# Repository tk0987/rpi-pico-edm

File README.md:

# rpi-pico-edm
jusst kicad - for a while

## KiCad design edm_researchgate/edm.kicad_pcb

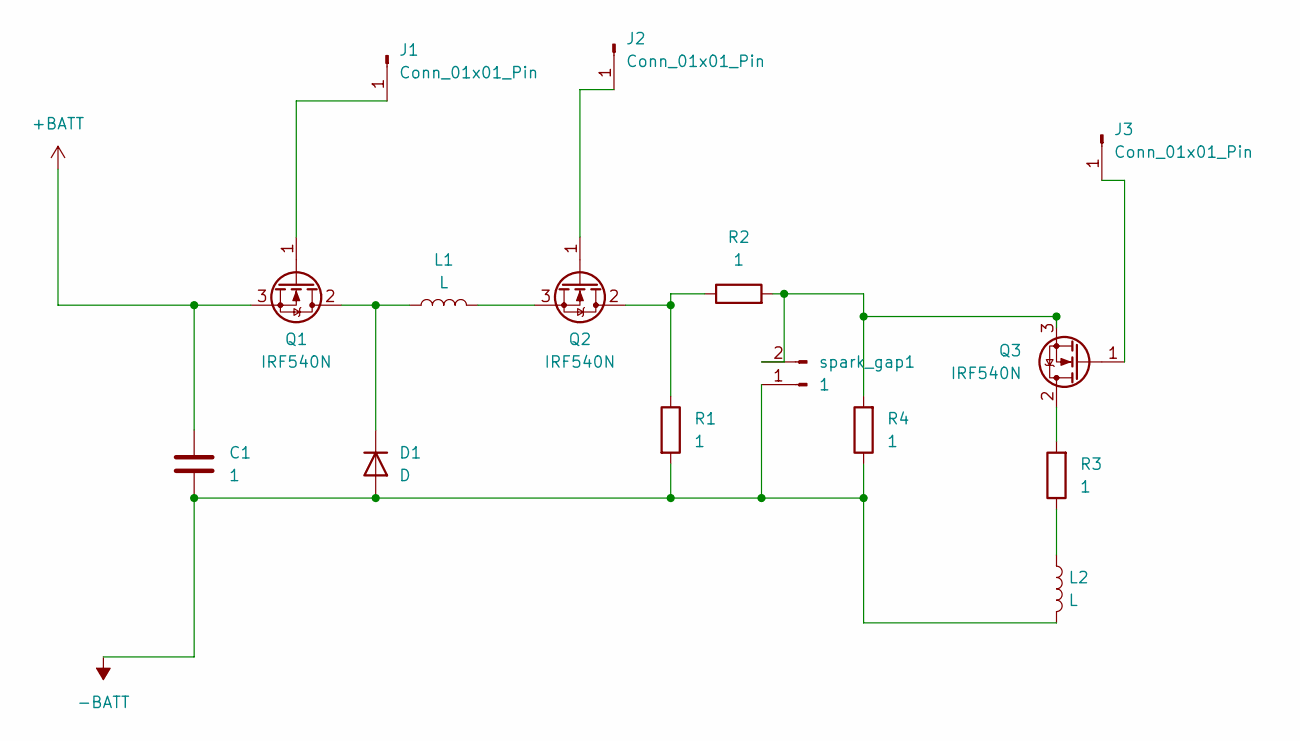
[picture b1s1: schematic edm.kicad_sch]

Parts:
C1: 1; CP_Axial_L37.0mm_D20.0mm_P43.00mm_Horizontal
D1: D; D_5KP_P10.16mm_Horizontal
J1, J2, J3: Conn_01x01_Pin; Pin_D0.7mm_L6.5mm_W1.8mm_FlatFork
L1, L2: L; D_5KP_P10.16mm_Horizontal
Q1, Q2, Q3: IRF540N; TO-220-3_Vertical
R1: 1; R_Axial_DIN0918_L18.0mm_D9.0mm_P25.40mm_Horizontal
R2, R3, R4: 1; R_Axial_DIN0414_L11.9mm_D4.5mm_P20.32mm_Horizontal
spark_gap1: 1; PinHeader_1x02_P2.54mm_Vertical

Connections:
+BATT: C1.1, Q1.3 (S)
-BATT: C1.2, D1.2 (A), L2.2, R1.2, R4.1, spark_gap1.1
unnamed: D1.1 (K), L1.1, Q1.2 (D)
unnamed: J1.1, Q1.1 (G)
unnamed: J2.1, Q2.1 (G)
unnamed: J3.1, Q3.1 (G)
unnamed: L2.1, R3.1
unnamed: Q2.2 (D), R1.1, R2.1
unnamed: L1.2, Q2.3 (S)
unnamed: Q3.2 (D), R3.2
unnamed: Q3.3 (S), R2.2, R4.2, spark_gap1.2

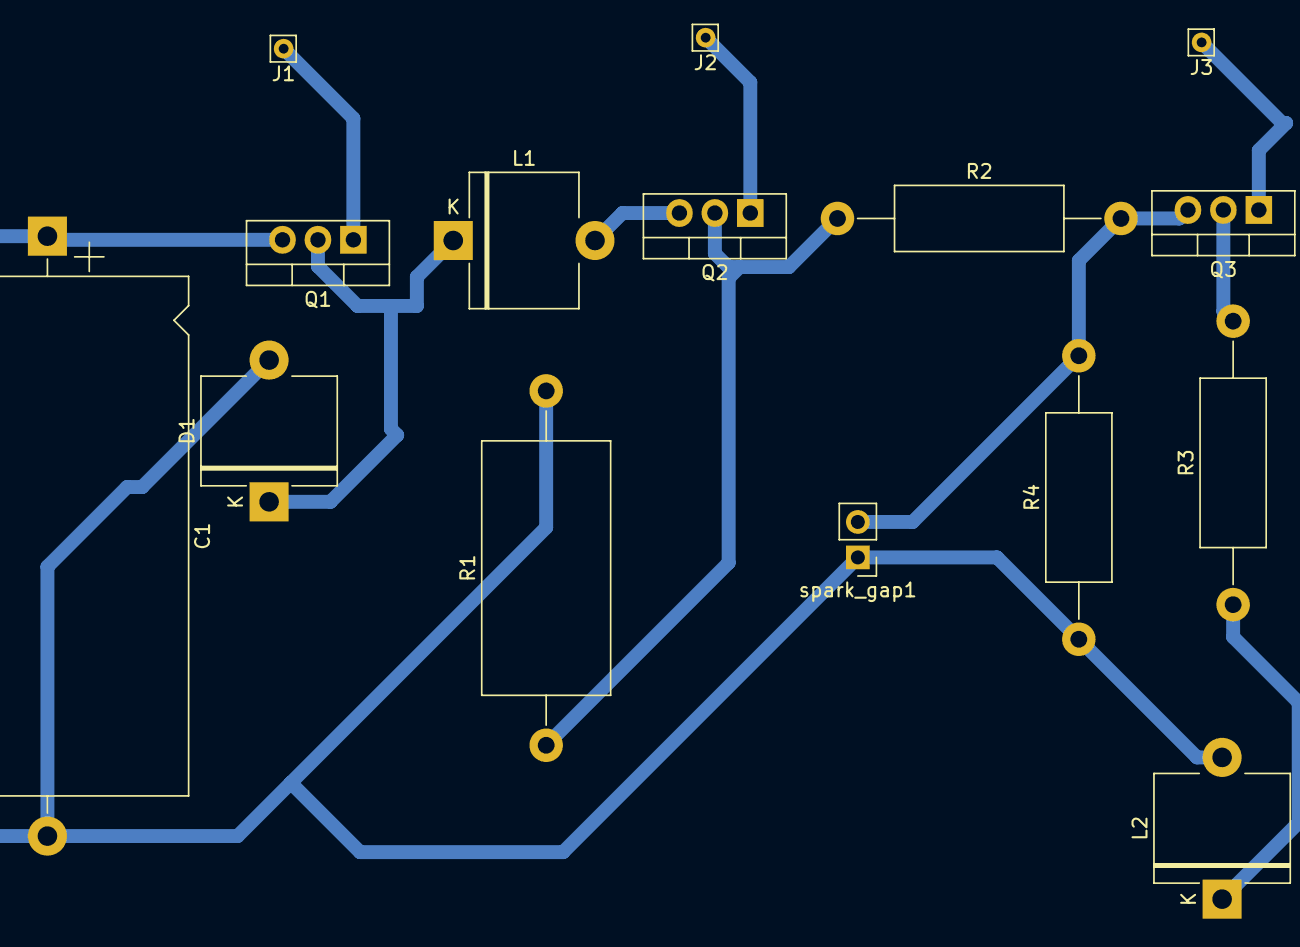
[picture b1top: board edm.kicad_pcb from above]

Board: 2 copper layers, 15 parts (0 on the bottom side), 11 nets.

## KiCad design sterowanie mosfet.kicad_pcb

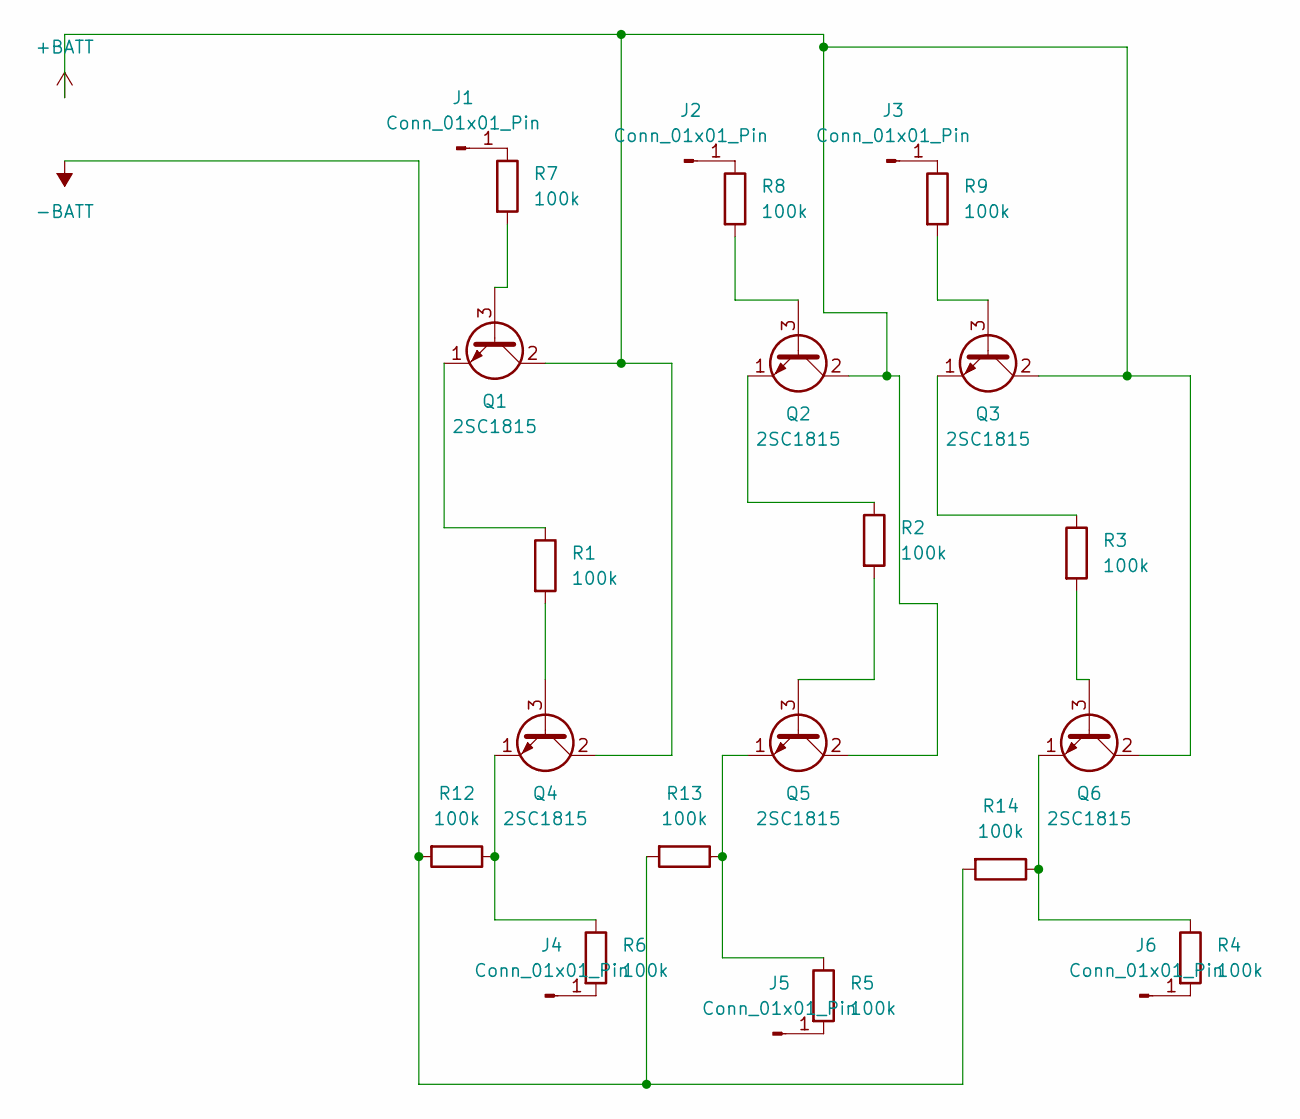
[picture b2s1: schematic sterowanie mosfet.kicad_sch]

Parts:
J1, J2, J3, J4, J5, J6: Conn_01x01_Pin; Pin_D1.0mm_L10.0mm
Q1, Q2, Q3, Q4, Q5, Q6: 2SC1815; TO-92_Inline
R1, R2, R3, R4, R5, R6, R7, R8, R9, R12, R13, R14: 100k; R_Axial_DIN0204_L3.6mm_D1.6mm_P5.08mm_Horizontal

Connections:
+BATT: Q1.2 (C), Q2.2 (C), Q3.2 (C), Q4.2 (C), Q5.2 (C), Q6.2 (C)
-BATT: R12.2, R13.2, R14.2
unnamed: J1.1, R7.1
unnamed: J2.1, R8.1
unnamed: J3.1, R9.1
unnamed: J4.1, R6.2
unnamed: J5.1, R5.2
unnamed: J6.1, R4.2
unnamed: Q1.3 (B), R7.2
unnamed: Q1.1 (E), R1.1
unnamed: Q2.3 (B), R8.2
unnamed: Q2.1 (E), R2.1
unnamed: Q3.3 (B), R9.2
unnamed: Q3.1 (E), R3.1
unnamed: Q4.3 (B), R1.2
unnamed: Q4.1 (E), R6.1, R12.1
unnamed: Q5.3 (B), R2.2
unnamed: Q5.1 (E), R5.1, R13.1
unnamed: Q6.3 (B), R3.2
unnamed: Q6.1 (E), R4.1, R14.1

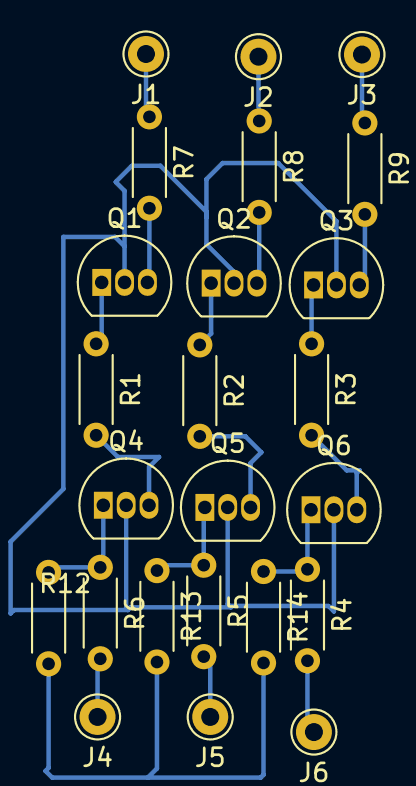
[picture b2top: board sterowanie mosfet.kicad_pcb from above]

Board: 2 copper layers, 24 parts (0 on the bottom side), 20 nets.

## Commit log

2024-07-18 from 3.3v to kinda 40 v relicate if need
2024-07-18 should to work after adjusment
